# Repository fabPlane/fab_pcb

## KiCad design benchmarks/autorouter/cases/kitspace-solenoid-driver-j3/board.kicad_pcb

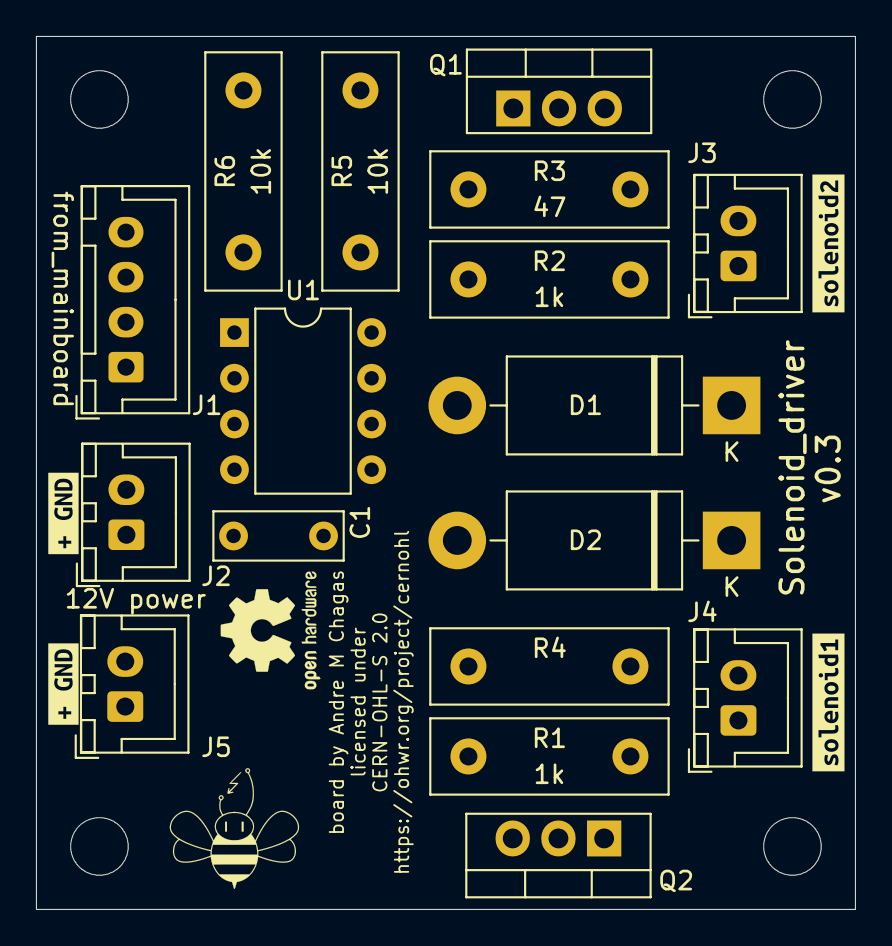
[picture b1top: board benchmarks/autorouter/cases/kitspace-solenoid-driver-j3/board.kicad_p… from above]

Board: 2 copper layers, 45.5 x 48.5 mm, 21 parts (0 on the bottom side), 10 nets, no tracks yet.

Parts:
C1: 100nF; C_Disc_D7.0mm_W2.5mm_P5.00mm
D1, D2: D_Schottky; D_DO-201AD_P15.24mm_Horizontal
J1: from_mainboard; JST_XH_B4B-XH-A_1x04_P2.50mm_Vertical
J2, J5: 12V power; JST_XH_B2B-XH-A_1x02_P2.50mm_Vertical
J3: to_solenoid2; JST_XH_B2B-XH-A_1x02_P2.50mm_Vertical
J4: to_solenoid1; JST_XH_B2B-XH-A_1x02_P2.50mm_Vertical
Q1, Q2: Q_NMOS_GDS; TO-220-3_Vertical
R1, R2: 1k; R_Box_L13.0mm_W4.0mm_P9.00mm
R3, R4: 47; R_Box_L13.0mm_W4.0mm_P9.00mm
R5, R6: 10k; R_Box_L13.0mm_W4.0mm_P9.00mm
U1: MIC4427; DIP-8_W7.62mm
kibuzzard-63063C94: G***; kibuzzard-63063C94
kibuzzard-63064E8E: G***; kibuzzard-63064E8E
kibuzzard-63064EFA: G***; kibuzzard-63064EFA
kibuzzard-63065932: G***; kibuzzard-63065932

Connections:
+12V: C1.1, D1.1 (K), D2.1 (K), J2.1, J3.1, J4.1, J5.1, U1.6 (V+)
GND: C1.2, J1.4, J2.2, J5.2, Q1.3 (S), Q2.3 (S), R1.1, R2.1, R5.1, R6.1, U1.3 (GND)
unnamed: D1.2 (A), J3.2, Q1.2 (D)
unnamed: D2.2 (A), J4.2, Q2.2 (D)
unnamed: J1.1, R5.2, U1.4 (IN_B)
unnamed: Q1.1 (G), R2.2, R3.1
unnamed: Q2.1 (G), R1.2, R4.1
unnamed: J1.2, R6.2, U1.2 (IN_A)
solenoid1: R3.2, U1.7 (OUT_A)
solenoid2: R4.2, U1.5 (OUT_B)

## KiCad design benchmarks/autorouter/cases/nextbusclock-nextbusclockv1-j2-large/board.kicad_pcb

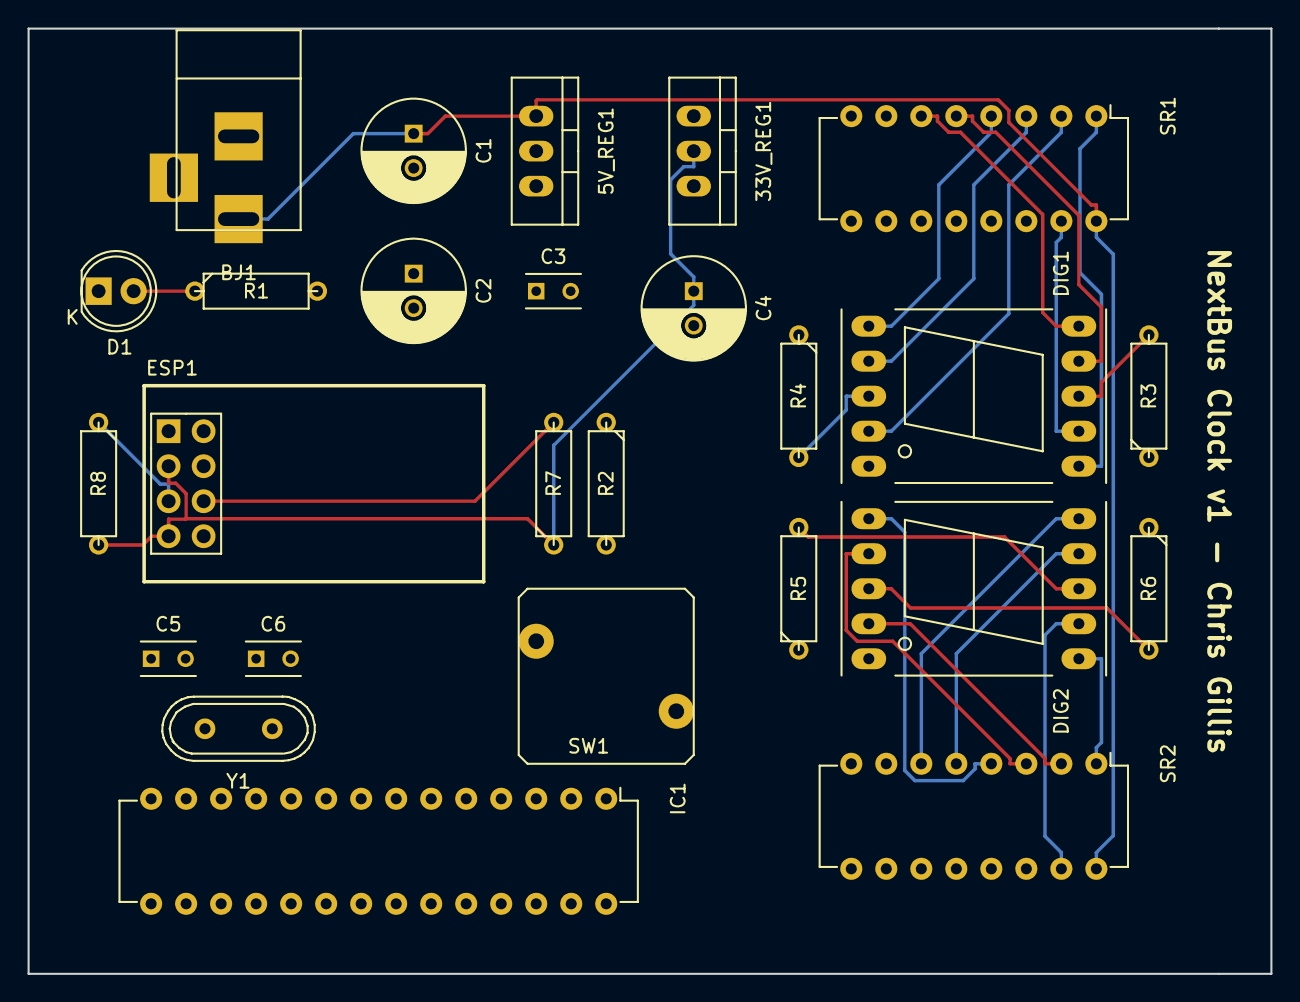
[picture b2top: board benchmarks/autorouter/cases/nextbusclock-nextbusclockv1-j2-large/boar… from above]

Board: 2 copper layers, 90.2 x 68.6 mm, 26 parts (0 on the bottom side), 33 nets.

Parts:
5V_REG1: LM7805; TO-220_Neutral123_Vertical
33V_REG1: LD1117V33; TO-220_Neutral123_Vertical
BJ1: BARREL_JACK
C1: 10uF; C_Radial_D7.5_L11.2_P2.5
C2: 1uF; C_Radial_D7.5_L11.2_P2.5
C3: 0.1uf; C_Rect_L4_W2.5_P2.5
C4: 10uf; C_Radial_D7.5_L11.2_P2.5
C5, C6: 22pF; C_Rect_L4_W2.5_P2.5
D1: PWR_LED; LED-5MM
DIG1, DIG2: LTS-6980HR; 7SegmentLED_LTS6760_LTS6780
ESP1: ESP-01
IC1: ATMEGA328-P; DIP-28_W7.62mm
R1: 1k; R3-5
R2, R7, R8: 10k; R3-5
R3, R4, R5, R6: 470; R3-5
SR1, SR2: 74HC595; DIP-16_W7.62mm
SW1: SW_PUSH
Y1: 16MHz; Crystal_HC49-U_Vertical

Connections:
/5V_PWR: 5V_REG1.3, 33V_REG1.3, C2.1, C3.1, IC1.7, IC1.20, IC1.21, R1.2, R2.1, SR1.10, SR2.10
/33V_PWR: 33V_REG1.2, C4.1, ESP1.3, ESP1.7, R7.1, R8.2
/ESP_RX: ESP1.8, IC1.3
/ESP_TX: ESP1.1, IC1.2
/SR_CLOCK: IC1.18, SR1.11, SR2.11
/SR_DATA: IC1.17, SR1.9, SR1.14, SR2.14
/SR_LATCH: IC1.14, SR1.12, SR2.12
GND: 5V_REG1.2, 33V_REG1.1, BJ1.2, BJ1.3, C1.2, C2.2, C3.2, C4.2, C5.1, C6.1, D1.1, ESP1.2, IC1.8, IC1.22, R3.1, R4.1, R5.1, R6.1, SR1.8, SR1.13, SR2.8, SR2.13, SW1.2
unnamed: C5.2, IC1.10, Y1.2
unnamed: C6.2, IC1.9, Y1.1
unnamed: D1.2, R1.1
unnamed: DIG1.1, SR1.4
unnamed: DIG1.2, SR1.3
unnamed: DIG1.3, R4.2
unnamed: DIG1.4, SR1.2
unnamed: DIG1.6, SR1.1
unnamed: DIG1.7, SR1.15
unnamed: DIG1.8, R3.2
unnamed: DIG1.9, SR1.5
unnamed: DIG1.10, SR1.6
unnamed: DIG2.1, SR2.4
unnamed: DIG2.2, SR2.3
unnamed: DIG2.3, R6.2
unnamed: DIG2.4, SR2.2
unnamed: DIG2.6, SR2.1
unnamed: DIG2.7, SR2.15
unnamed: DIG2.8, R5.2
unnamed: DIG2.9, SR2.5
unnamed: DIG2.10, SR2.6
unnamed: ESP1.5, R8.1
unnamed: ESP1.6, R7.2
unnamed: IC1.1, R2.2, SW1.1
VCC: 5V_REG1.1, BJ1.1, C1.1, SR1.16, SR2.16

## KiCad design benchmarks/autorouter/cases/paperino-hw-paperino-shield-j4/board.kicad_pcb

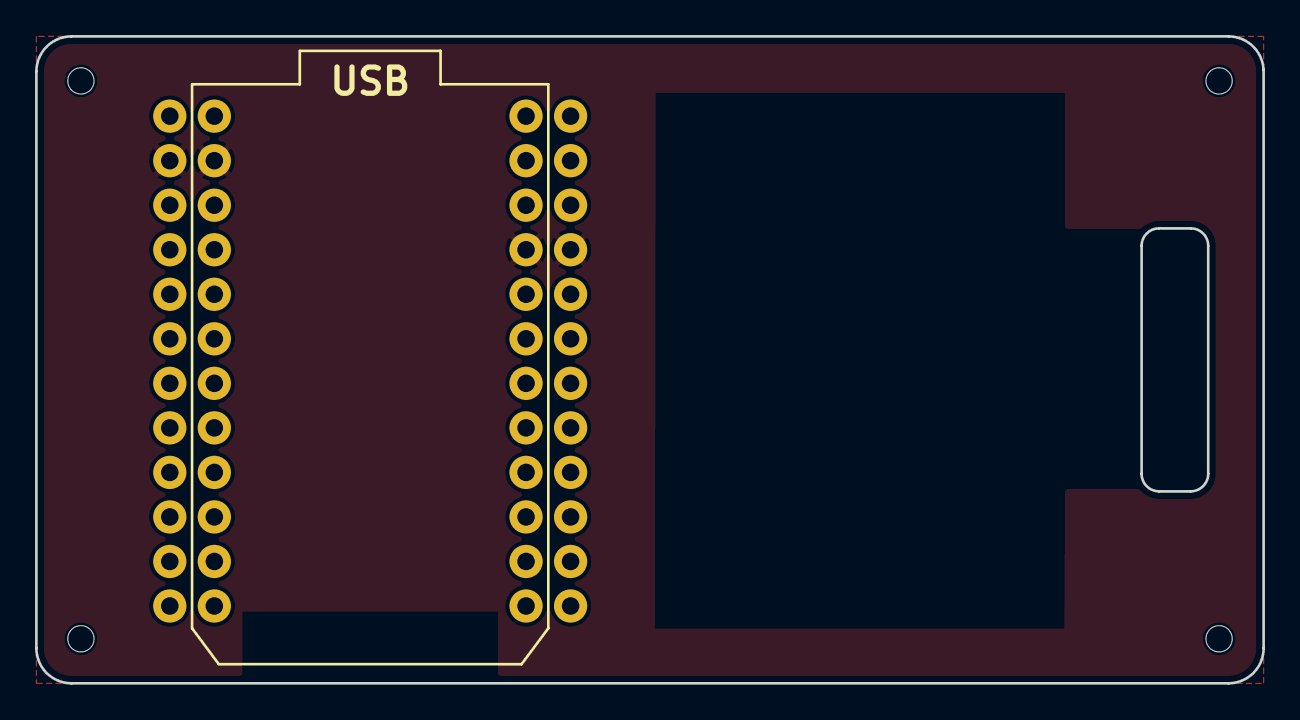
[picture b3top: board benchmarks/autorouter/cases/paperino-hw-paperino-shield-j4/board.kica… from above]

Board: 2 copper layers, 70.0 x 36.9 mm, 6 parts (1 on the bottom side), 11 nets, no tracks yet.

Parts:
A1: Photon; photon_headers
A2: paperino_module
M1, M2, M3, M4: Mounting_hole; mounting_hole_1.5

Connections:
+3V3: A1.24, A2.1
/INT1: A1.5, A2.6
/INT2: A1.18, A2.5
/SPI_CLK: A1.9, A2.9
/SPI_CS1: A1.10, A2.10
/SPI_CS2: A1.19, A2.4
/SPI_MISO: A1.8, A2.7
/SPI_MOSI: A1.7, A2.8
/~BUSY: A1.11, A2.12
/~RST: A1.12, A2.11
GND: A1.2, A1.21, A2.2

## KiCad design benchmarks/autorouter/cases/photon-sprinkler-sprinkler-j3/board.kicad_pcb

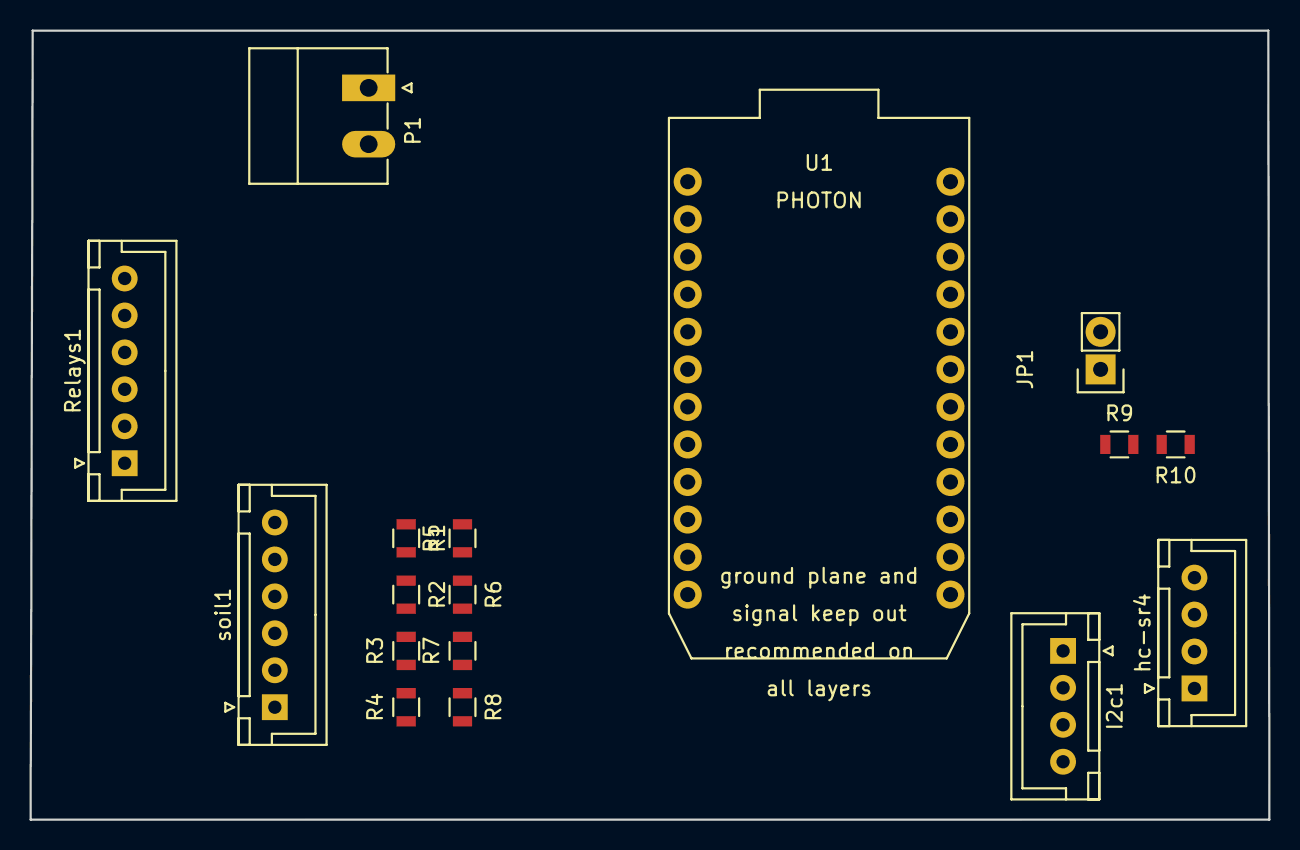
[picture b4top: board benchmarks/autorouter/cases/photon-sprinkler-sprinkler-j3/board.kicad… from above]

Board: 2 copper layers, 83.8 x 53.4 mm, 17 parts (0 on the bottom side), 21 nets, no tracks yet.

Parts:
I2c1: CONN_01X04; JST_XH_B04B-XH-A_04x2.50mm_Straight
JP1: CONN_01X02; Socket_Strip_Straight_1x02
P1: CONN_01X02; PhoenixContact_MC-G_02x3.81mm_Angled
R1, R2, R3, R4, R5, R6, R7, R8, R9, R10: R; R_0805
Relays1: CONN_01X06; JST_XH_B06B-XH-A_06x2.50mm_Straight
U1: PHOTON
hc-sr4: CONN_01X04; JST_XH_B04B-XH-A_04x2.50mm_Straight
soil1: CONN_01X06; JST_XH_B06B-XH-A_06x2.50mm_Straight

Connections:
+3V3: I2c1.1, JP1.2, U1.24
+5V: P1.2, Relays1.1, U1.1, hc-sr4.1, soil1.1
GND: I2c1.4, P1.1, R5.1, R6.1, R7.1, R8.1, R9.1, Relays1.6, U1.2, hc-sr4.4, soil1.6
unnamed: I2c1.2, U1.14
unnamed: I2c1.3, U1.13
unnamed: JP1.1, U1.22
unnamed: R1.1, R5.2, U1.9
unnamed: R1.2, soil1.5
unnamed: R2.1, R6.2, U1.10
unnamed: R2.2, soil1.4
unnamed: R3.1, R7.2, U1.11
unnamed: R3.2, soil1.3
unnamed: R4.1, R8.2, U1.12
unnamed: R4.2, soil1.2
unnamed: R10.1, hc-sr4.2
unnamed: R9.2, R10.2, U1.18
unnamed: Relays1.2, U1.8
unnamed: Relays1.3, U1.7
unnamed: Relays1.4, U1.6
unnamed: Relays1.5, U1.5
unnamed: U1.17, hc-sr4.3

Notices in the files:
benchmarks/autorouter/cases/kitspace-solenoid-driver-j3/board.kicad_pcb:
licensed under
CERN-OHL-S 2.0
benchmarks/autorouter/cases/paperino-hw-paperino-shield-j4/board.kicad_pcb:
licensed under CC-BY 4.0
